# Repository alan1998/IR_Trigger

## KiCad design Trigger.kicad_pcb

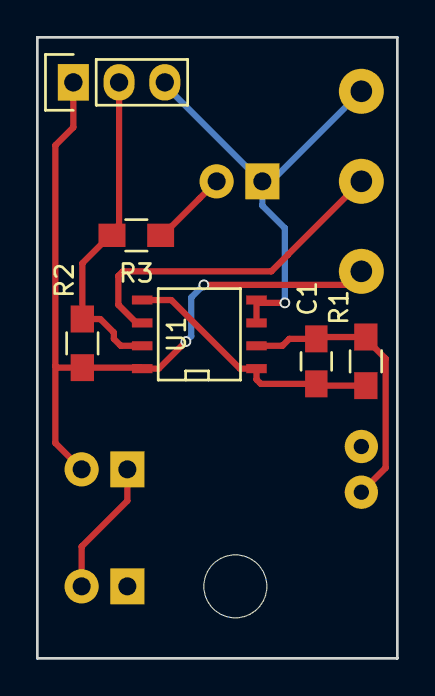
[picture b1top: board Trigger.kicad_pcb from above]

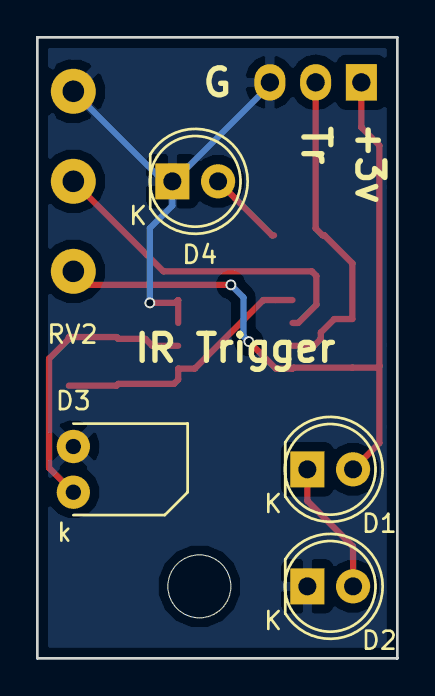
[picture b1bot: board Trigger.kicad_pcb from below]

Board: 2 copper layers, 20.0 x 34.5 mm, 12 parts (5 on the bottom side), 8 nets.

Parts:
C1: 10n; C_0805_HandSoldering
D1, D2, D4: LED; LED-5MM
D3: LED; PhotoDiode
H1: MountHole; MountingHole_3.5mm
P1: CONN_01X03; Pin_Header_Straight_1x03
R1: 100k; R_0805_HandSoldering
R2: 100K; R_0805_HandSoldering
R3: 220R; R_0805_HandSoldering
RV2: POT; Potentiometer_WirePads_largePads
U1: MCP6002; SOIC-8-N

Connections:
+3V3: D1.2, P1.1, R2.2, RV2.1, U1.8
GND: D2.1, D3.2, D4.1, P1.3, RV2.3, U1.3, U1.4
unnamed: C1.1, R1.1, U1.1, U1.5
unnamed: C1.2, D3.1, R1.2, U1.2
unnamed: D1.1, D2.2
unnamed: D4.2, R3.1
unnamed: P1.2, R2.1, R3.2, U1.7
unnamed: RV2.2, U1.6

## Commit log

2016-10-09 First
2016-10-10 Layout
2016-10-10 As submitted
2016-10-12 Add part nos to Schematic
